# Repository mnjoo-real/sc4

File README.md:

# Singing capacitor — pre-experiment numerical model

## PCB ordering — start here

A validated PCB fabrication package for all 5 board variants exists under
[`pcb/`](pcb/). This section is a navigation index only — the files linked
below are the source of truth; nothing here duplicates their content.

**Start here:**
[`pcb/v0.3.1_FABRICATION_PACKAGE_SUMMARY.md`](pcb/v0.3.1_FABRICATION_PACKAGE_SUMMARY.md)

This is the top-level summary of the current PCB fabrication package and
records whether each board variant has passed the required KiCad/DRC/
Gerber/drill/visual checks.

For detailed per-board validation — including the authoritative
`READY_FOR_JLCPCB` status for each variant — see
[`pcb/FABRICATION_REVIEW.md`](pcb/FABRICATION_REVIEW.md). **Only order a
board whose entry there is marked ready.**

### The five board variants

    S90-0402
    S90-0603
    S90-0805
    W90-0603
    S0-0603

### Where the actual files are, per variant

| what | where | for |
|---|---|---|
| Editable KiCad source | `pcb/<variant>/<variant>.kicad_pcb` | opening/editing in KiCad |
| Raw Gerber + drill files | `pcb/<variant>/manufacturing/gerbers/` | inspection, not direct upload |
| **JLCPCB upload archive** | `pcb/<variant>/manufacturing/<variant>_JLCPCB_Gerber.zip` | **upload this to JLCPCB** |
| Gerber verification images | `pcb/<variant>/manufacturing/gerber_verification/` | checking the export against the design before ordering |
| KiCad 3D renders | `pcb/<variant>/renders/` | visual sanity-check, not fabrication input |

**The `*_JLCPCB_Gerber.zip` file is the file to upload to JLCPCB.** Do not
upload the `.kicad_pcb`/`.kicad_pro` source files, the PNG renders, or the
DRC/validation reports — those are for review, not fabrication input.

The five current upload archives:

- [`pcb/S90-0402/manufacturing/S90-0402_JLCPCB_Gerber.zip`](pcb/S90-0402/manufacturing/S90-0402_JLCPCB_Gerber.zip)
- [`pcb/S90-0603/manufacturing/S90-0603_JLCPCB_Gerber.zip`](pcb/S90-0603/manufacturing/S90-0603_JLCPCB_Gerber.zip)
- [`pcb/S90-0805/manufacturing/S90-0805_JLCPCB_Gerber.zip`](pcb/S90-0805/manufacturing/S90-0805_JLCPCB_Gerber.zip)
- [`pcb/W90-0603/manufacturing/W90-0603_JLCPCB_Gerber.zip`](pcb/W90-0603/manufacturing/W90-0603_JLCPCB_Gerber.zip)
- [`pcb/S0-0603/manufacturing/S0-0603_JLCPCB_Gerber.zip`](pcb/S0-0603/manufacturing/S0-0603_JLCPCB_Gerber.zip)

### Before ordering — read in this order

1. [`pcb/v0.3.1_FABRICATION_PACKAGE_SUMMARY.md`](pcb/v0.3.1_FABRICATION_PACKAGE_SUMMARY.md) — current fabrication-package summary.
2. [`pcb/FABRICATION_REVIEW.md`](pcb/FABRICATION_REVIEW.md) — detailed per-board validation, `READY_FOR_JLCPCB` status, and the Gerber/drill/render file map.
3. [`design/jlcpcb_order_settings.csv`](design/jlcpcb_order_settings.csv) — the JLCPCB fabrication options to select on the quote/order page (material, layers, thickness, copper weight, surface finish, etc.).
4. [`design/pcb_quantity_plan.csv`](design/pcb_quantity_plan.csv) — planned bare-PCB order quantities, per variant.
5. [`design/board_population_plan.csv`](design/board_population_plan.csv) — how the ordered boards are intended to be populated with MLCCs for the experiment.
6. [`design/PCB_FABRICATION_SPEC.md`](design/PCB_FABRICATION_SPEC.md) — detailed fabrication/design rationale and the common board specification.
7. [`design/PCB_CAD_ASSUMPTIONS.md`](design/PCB_CAD_ASSUMPTIONS.md) — fabrication/CAD parameters not originally fixed in v0.3.0, and the assumptions/fixes made while generating the KiCad files.

**⚠ Quantity check before the final order:** `pcb_quantity_plan.csv` is the
order-quantity source; `board_population_plan.csv` is the specimen
population source, and should be checked against it before the final
purchase. As of this writing they **do not agree for S90-0603**:
`board_population_plan.csv` calls for 15 populated S90-0603 specimens
(R×3, C1×2, C2×2, V1×2, V2×2, V3×2, N1×2), but
`pcb_quantity_plan.csv` currently plans to order only 5 S90-0603 boards.
The other four variants (S90-0402, S90-0805, W90-0603, S0-0603) agree
(5 planned = 5 needed each). Before placing the final order, verify that
the fabrication quantity plan covers the specimen population plan — this
README does not resolve that inconsistency, and the quantity was not
guessed here.

### Placing the order

1. Open `pcb/v0.3.1_FABRICATION_PACKAGE_SUMMARY.md`.
2. Confirm the desired board is marked ready in `pcb/FABRICATION_REVIEW.md`.
3. Open `design/jlcpcb_order_settings.csv`.
4. Open `design/pcb_quantity_plan.csv` (and cross-check against
   `board_population_plan.csv` per the warning above).
5. Upload that variant's `*_JLCPCB_Gerber.zip` to JLCPCB.
6. Confirm that JLCPCB correctly detects the board (outline, layer count,
   size).
7. Apply the fabrication options from `jlcpcb_order_settings.csv`.
8. Set the quantity from the current quantity plan.
9. Inspect the online Gerber preview (checklist below).
10. Only then proceed to fabrication/payment.

`design/jlcpcb_order_settings.csv` remains the source of truth for the
actual option selections — the JLCPCB UI's exact labels aren't reproduced
here.

### What to check in the JLCPCB Gerber viewer

Before paying, visually compare JLCPCB's preview against this repository's
verified artifacts and confirm, at minimum:

- board outline appears correct,
- four mounting holes are present,
- the MLCC footprint is present at the intended position,
- S90 vs. S0 orientation is visibly different where intended,
- top copper traces are present,
- there is no unexpected bottom copper,
- solder-mask openings are present over the intended pads,
- no obvious trace or outline is missing.

Reference images for this comparison:

- `pcb/<variant>/manufacturing/gerber_verification/` — most relevant for
  fabrication inspection, since these are rendered directly from the
  exported Gerbers:
  `<variant>_composite_top.png`, `<variant>_top_copper.png`,
  `<variant>_solder_mask.png`, `<variant>_silkscreen.png`,
  `<variant>_edge_cuts.png`
- `pcb/<variant>/renders/` — real KiCad top/bottom/perspective 3D renders
  (useful, but decorative relative to the Gerber-verification images above)
- [`pcb/PCB_5_VARIANT_COMPARISON.png`](pcb/PCB_5_VARIANT_COMPARISON.png) — all five variants at the same scale, for a quick overview

### Bare PCB vs. assembly

The `*_JLCPCB_Gerber.zip` files are **PCB fabrication files only**.
Uploading one orders a **bare PCB** — MLCC assembly is **not** included.
See [`design/board_population_plan.csv`](design/board_population_plan.csv)
for the intended capacitor population per board. Assembly (PCBA) is a
separate deliverable, not covered by this package.

### Directory map

```
pcb/
├── v0.3.1_FABRICATION_PACKAGE_SUMMARY.md
├── FABRICATION_REVIEW.md
├── PCB_5_VARIANT_COMPARISON.png
├── S90-0402/
│   ├── S90-0402.kicad_pcb
│   ├── manufacturing/
│   │   ├── S90-0402_JLCPCB_Gerber.zip   <- upload this to JLCPCB
│   │   ├── gerbers/
│   │   ├── drc_report.txt
│   │   ├── drill_report.txt
│   │   └── gerber_verification/
│   └── renders/
├── S90-0603/
├── S90-0805/
├── W90-0603/
└── S0-0603/
```

```
design/
├── jlcpcb_order_settings.csv
├── pcb_quantity_plan.csv
├── board_population_plan.csv
├── PCB_FABRICATION_SPEC.md
└── PCB_CAD_ASSUMPTIONS.md
```

---

A lightweight simulation for planning a *singing capacitor* experiment before
ordering the PCB and MLCCs.

The goal is **not** to predict the exact sound level of a commercial capacitor.
Instead, the model is used to decide:

- what PCB size and thickness to order,
- where to place the MLCC on the PCB,
- which orientation to use,
- what frequency range to sweep,
- and which conditions should produce a strong or weak vibration response.

The model deliberately keeps only the physics needed for those design choices.

---

## 1. The physics being modelled

A Class-II ceramic MLCC such as X5R or X7R deforms when an electric field is
applied. The first-order electromechanical model is

    S = dE + M E²

where `S` is strain, `d` is the piezoelectric coefficient, `M` is the
electrostrictive coefficient, and `E` is the electric field.

For

    E(t) = E_DC + E_AC cos(ωt)

the strain contains two important vibration components:

    A₁ cos(ωt),        A₁ = (d + 2 M E_DC) E_AC
    A₂ cos(2ωt),       A₂ = ½ M E_AC²

so an electrical excitation at frequency `f` can mechanically excite the PCB
at both

    f          fundamental
    2f         second harmonic

The second harmonic is important because it can hit a PCB resonance even when
the electrical excitation frequency itself does not.

For the first version of the simulation, the exact `d` and `M` of a commercial
MLCC are **not required**. The capacitor is treated as a relative vibration
source with configurable strengths at `f` and `2f`.

### PCB resonance

The PCB is approximated as a rectangular thin plate.

Its bending rigidity is

    D = E h³ / [12(1 − ν²)]

where `E` is the effective Young's modulus of the PCB, `h` is PCB thickness,
and `ν` is Poisson's ratio.

For a simply supported rectangular plate with length `a` and width `b`,

    φ_mn(x,y) = sin(mπx/a) sin(nπy/b)

and the natural frequencies are

    ω_mn = π² √(D / ρh) · (m²/a² + n²/b²)

    f_mn = ω_mn / 2π

This is not intended to reproduce a real clamped PCB exactly. It is sufficient
for finding the main trends:

- a larger PCB gives lower resonant frequencies,
- a thicker PCB gives higher resonant frequencies,
- different MLCC positions couple differently to each mode.

### MLCC position and orientation

The MLCC does not excite every PCB mode equally.

For a simple point-force source,

    coupling ∝ φ_mn(x_c, y_c)

so a capacitor near a modal antinode excites that mode strongly, while one near
a node excites it weakly.

The soldered MLCC also acts approximately like a small force couple / moment.
For that case the coupling is related to the slope of the mode shape:

    x-oriented MLCC:  coupling ∝ ∂φ_mn/∂x
    y-oriented MLCC:  coupling ∝ ∂φ_mn/∂y

This is why rotating the same MLCC by 90° can change the PCB vibration.

The simulation therefore focuses on the chain

    voltage
      ↓
    relative MLCC source at f and 2f
      ↓
    PCB mode coupling
      ↓
    PCB vibration response

rather than trying to model every internal ceramic layer.

---

## 2. What the code actually does

### MLCC source (`source.py`)

The capacitor is represented by two harmonic source components:

    source_f  = C₁ · A₁
    source_2f = C₂ · A₂

For the initial model, `C₁` and `C₂` are simply configurable scale factors.

If real electromechanical coefficients are unavailable, the code can instead
use normalized source strengths such as

    source_f  = 1
    source_2f = r_harmonic

so PCB design can be studied independently of the uncertain absolute MLCC
vibration amplitude.

The important output is therefore **relative response**, not absolute SPL.

### PCB (`plate.py`)

The PCB is an isotropic rectangular thin plate with configurable

    length
    width
    thickness
    Young's modulus
    density
    Poisson ratio
    damping

The code computes the first several `(m,n)` modes analytically.

The default reference geometry is the one used in Kim et al. (2019):

    100 mm × 40 mm × 1.0 mm

This is only a baseline. The simulation sweeps several nearby geometries to find
a board that has clear resonances in the experimental frequency range.

### Coupling (`coupling.py`)

For each candidate MLCC position and orientation, the code evaluates how
strongly the source couples to every PCB mode.

The main scan is

    x/a = 0.20, 0.35, 0.50, 0.65, 0.80
    y/b = 0.25, 0.50, 0.75
    orientation = 0°, 90°

This produces both

- a **high-coupling position** for a clear singing-capacitor demonstration,
- and a **low-coupling position** that can be used as a control.

### Frequency response (`response.py`)

Each PCB mode is treated as a damped harmonic oscillator:

    q_n(ω) =
        Q_n /
        [m_n(ω_n² − ω² + i 2ζ_n ω_n ω)]

The modal responses are summed to obtain relative PCB displacement and velocity.

The simulation evaluates the response at both

    f
    2f

for each electrical excitation frequency.

The main plotted quantity is PCB velocity amplitude, used only as a
**vibration / acoustic-noise proxy**.

No acoustic radiation model is included.

### Sweep (`run_sweep.py`)

The first design sweep varies

    PCB length       60, 80, 100 mm
    PCB width        30, 40 mm
    PCB thickness    0.8, 1.0, 1.6 mm

and scans excitation frequencies over

    200–3000 Hz

with a coarse step first, followed by a finer scan near predicted resonances.

After the PCB geometry is selected, the code scans MLCC position and orientation.

The simulation is therefore used in this order:

    1. choose PCB geometry
    2. find PCB resonances
    3. choose MLCC position
    4. compare 0° and 90° orientation
    5. choose useful excitation frequencies
    6. define strong-response and weak-response experimental conditions

---

## 3. Validation (`test_model.py`)

The model only needs simple checks because it is an experiment-design tool, not
a high-fidelity FEM solver.

| check | expected result |
|---|---|
| increasing PCB length | resonant frequencies decrease |
| increasing PCB thickness | resonant frequencies increase |
| mode shape at supported edge | approximately zero |
| MLCC placed at a modal node | weak point-force coupling |
| MLCC placed at an antinode | strong point-force coupling |
| rotate MLCC by 90° | x/y moment coupling changes |
| increase damping | resonance peak becomes lower and broader |
| electrostrictive source | response can appear at `2f` |

The code should also reproduce the analytical strain amplitudes

    A₁ = (d + 2 M E_DC) E_AC
    A₂ = ½ M E_AC²

for a synthetic test case.

Synthetic coefficients are used only to check the equations; they must not be
presented as properties of a real commercial MLCC.

---

## 4. Outputs

### `fig1_modes.png`

The first PCB mode shapes and their natural frequencies for the baseline

    100 × 40 × 1 mm

board.

This shows which PCB modes lie inside the planned excitation range.

### `fig2_geometry_sweep.png`

Predicted resonant frequencies for different PCB sizes and thicknesses.

This is the main figure for deciding **which PCB to order**.

A useful board should have:

- at least a few resonances inside the measurable frequency range,
- resonances separated enough to identify experimentally,
- and no extreme sensitivity to small geometry changes.

### `fig3_frequency_response.png`

Relative PCB vibration versus electrical excitation frequency.

Both mechanical components are shown:

    response at f
    response at 2f

A strong peak occurs when either `f` or `2f` approaches a PCB resonance.

This figure determines which frequency ranges should be scanned more densely in
the real experiment.

### `fig4_position_map.png`

Heatmap of predicted vibration versus MLCC position.

This is used to choose

- one high-response capacitor location,
- one low-response control location.

### `fig5_orientation.png`

Comparison of the same MLCC position at

    0°
    90°

to determine whether orientation should be included as an experimental variable.

### `recommended_setup.csv`

Final summary produced by the sweep:

| parameter | recommended value |
|---|---|
| PCB length | simulation result |
| PCB width | simulation result |
| PCB thickness | simulation result |
| MLCC x-position | simulation result |
| MLCC y-position | simulation result |
| MLCC orientation | simulation result |
| main frequency range | simulation result |
| resonance frequencies | simulation result |
| strong-response condition | simulation result |
| control condition | simulation result |

The code should not fill this table with hard-coded recommendations. Values are
written only after the sweep has been run.

---

## 5. Running it

```bash
pip install numpy scipy matplotlib pandas

python test_model.py
python run_modes.py
python run_sweep.py geometry
python run_sweep.py position
python run_sweep.py all
```

All figures and tables are written to

```text
out/
```

Suggested repository structure:

```text
singing-capacitor/
│
├── README.md
├── model.py
├── source.py
├── plate.py
├── coupling.py
├── response.py
├── test_model.py
├── run_modes.py
├── run_sweep.py
└── out/
```

The main parameters should be collected in one dataclass:

```python
from dataclasses import dataclass

@dataclass
class Params:
    pcb_L: float = 0.100
    pcb_W: float = 0.040
    pcb_h: float = 0.001

    E_pcb: float = 20e9
    rho_pcb: float = 1850.0
    nu_pcb: float = 0.13
    damping: float = 0.02

    mlcc_x_frac: float = 0.50
    mlcc_y_frac: float = 0.50
    orientation_deg: float = 0.0

    f_min: float = 200.0
    f_max: float = 3000.0
```

The exact effective FR-4 material constants are uncertain, so these values are
configuration parameters rather than fixed physical truths.

---

## 6. Known limitations — worth stating in a report

* The PCB is an **isotropic simply supported thin plate**. A real FR-4 PCB is
  anisotropic and the experimental bolts/clamps change its natural frequencies.
  The model should therefore be used for geometry selection and qualitative
  trends, not exact resonance prediction.

* The MLCC is represented as a **lumped harmonic source**, not as hundreds of
  dielectric and electrode layers. This is deliberate: the purpose is to choose
  the experimental PCB and setup before the exact commercial MLCC properties
  are known.

* Exact piezoelectric and electrostrictive coefficients of commercial MLCCs are
  usually unavailable. Unless experimentally measured values are supplied, the
  simulation should compare **relative source amplitudes**, not claim absolute
  capacitor vibration.

* Solder geometry is not explicitly modelled. Its effect is absorbed into the
  equivalent source / moment coupling.

* The first model does not calculate sound pressure. PCB velocity is used as a
  proxy for how strongly the board is likely to radiate sound.

* Absolute resonance frequencies will shift after the real PCB is manufactured
  and mounted. After the first PCB is measured, the effective material and
  damping parameters can be calibrated and the simulation rerun.

---

## 7. What this simulation must decide before ordering

The model is successful if it answers these practical questions:

1. Should the PCB be approximately `60`, `80`, or `100 mm` long?
2. Should its thickness be `0.8`, `1.0`, or `1.6 mm`?
3. Which resonances fall inside the planned excitation range?
4. Where should the MLCC be soldered for a strong response?
5. Where should a control MLCC be soldered for a weak response?
6. Does rotating the MLCC by 90° produce a useful difference?
7. Which electrical frequencies should be scanned densely in the real test?
8. Is the response dominated by the fundamental `f`, the second harmonic `2f`,
   or both?

Once these are answered, the PCB can be ordered and the detailed MLCC
comparison can be designed around the selected board.

The key principle is:

    keep the model only as complicated as necessary
    to make the experimental setup decision.

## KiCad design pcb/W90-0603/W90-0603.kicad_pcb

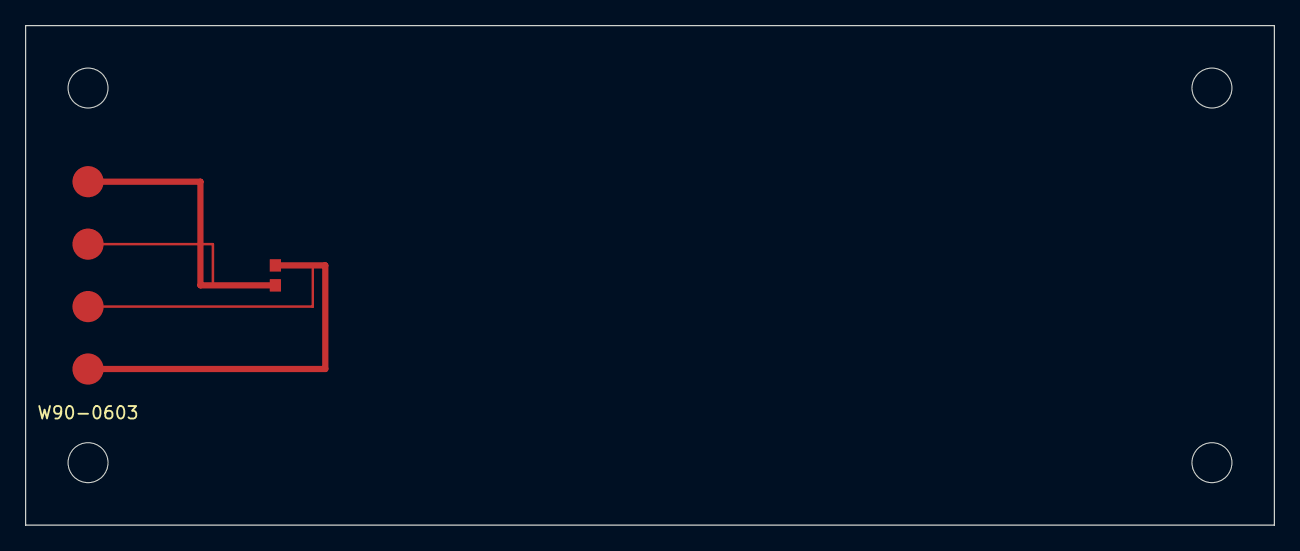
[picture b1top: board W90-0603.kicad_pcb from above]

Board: 2 copper layers, 100.0 x 40.0 mm, 9 parts (0 on the bottom side), 2 nets.

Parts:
DRIVE+: EdgeContact; EdgeContact_2.5mm_Round
DRIVE-: EdgeContact; EdgeContact_2.5mm_Round
H1, H2, H3, H4: NPTH_3.2mm
MLCC1: C_0603; C_0603_Local
SENSE+: EdgeContact; EdgeContact_2.5mm_Round
SENSE-: EdgeContact; EdgeContact_2.5mm_Round

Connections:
DRIVE_SENSE_MINUS: DRIVE-.1, MLCC1.2, SENSE-.1
DRIVE_SENSE_PLUS: DRIVE+.1, MLCC1.1, SENSE+.1
